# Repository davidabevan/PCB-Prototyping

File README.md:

# PCB-Prototyping
Eagle Cad/Fritzing Footprints for hard to find parts.

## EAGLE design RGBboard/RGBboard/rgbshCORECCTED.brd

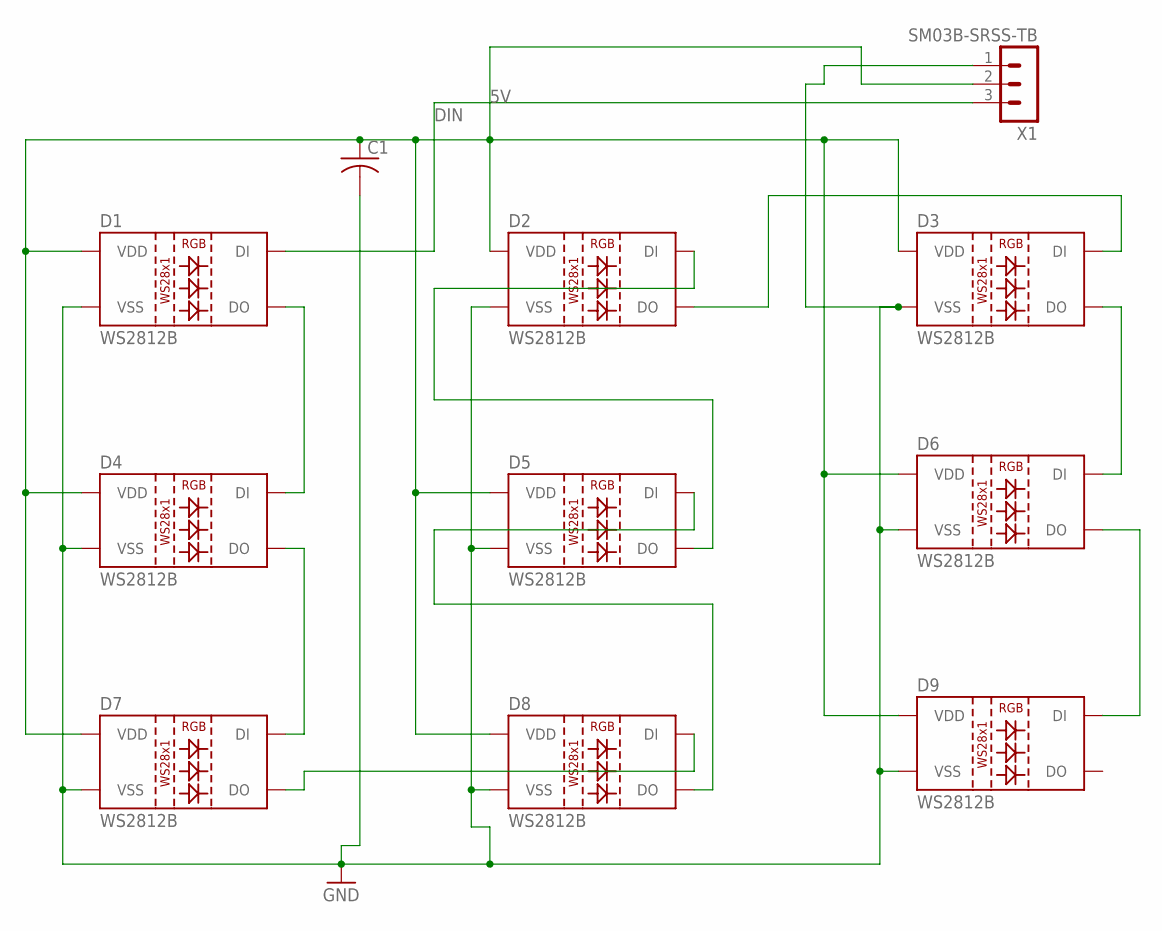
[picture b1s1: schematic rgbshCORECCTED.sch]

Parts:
C1: C-USC0805K; C0805K
D1, D2, D3, D4, D5, D6, D7, D8, D9: WS2812B
X1: SM03B-SRSS-TB

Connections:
5V: C1.1, D1.1 (VDD), D2.1 (VDD), D3.1 (VDD), D4.1 (VDD), D5.1 (VDD), D6.1 (VDD), D7.1 (VDD), D8.1 (VDD), D9.1 (VDD), X1.2
DIN: D1.4 (DI), X1.3
GND: C1.2, D1.3 (VSS), D2.3 (VSS), D3.3 (VSS), D4.3 (VSS), D5.3 (VSS), D6.3 (VSS), D7.3 (VSS), D8.3 (VSS), D9.3 (VSS), X1.1
unnamed: D1.2 (DO), D4.4 (DI)
unnamed: D4.2 (DO), D7.4 (DI)
unnamed: D7.2 (DO), D8.4 (DI)
unnamed: D5.4 (DI), D8.2 (DO)
unnamed: D2.4 (DI), D5.2 (DO)
unnamed: D2.2 (DO), D3.4 (DI)
unnamed: D3.2 (DO), D6.4 (DI)
unnamed: D6.2 (DO), D9.4 (DI)

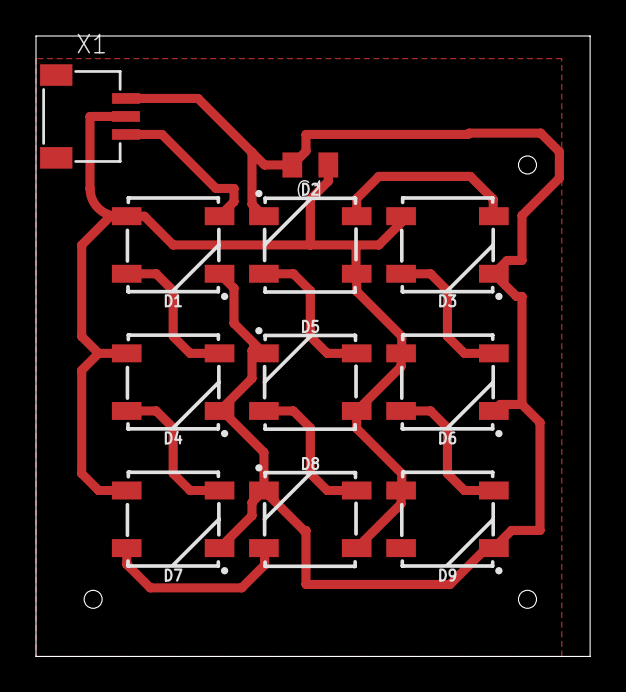
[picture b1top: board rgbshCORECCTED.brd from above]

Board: 2 copper layers, 30.8 x 34.5 mm, 11 parts (0 on the bottom side), 11 nets.

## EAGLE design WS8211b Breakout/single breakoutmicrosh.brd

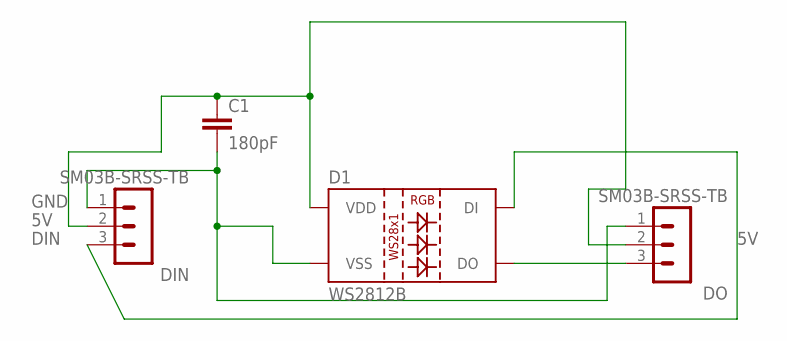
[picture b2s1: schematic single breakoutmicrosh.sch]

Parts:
C1: 180pF; 0603
D1: WS2812B
DIN: SM03B-SRSS-TB
DO: SM03B-SRSS-TB

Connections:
5V: C1.1, D1.1 (VDD), DIN.2, DO.2
DIN: D1.4 (DI), DIN.3
DO: D1.2 (DO), DO.3
GND: C1.2, D1.3 (VSS), DIN.1, DO.1

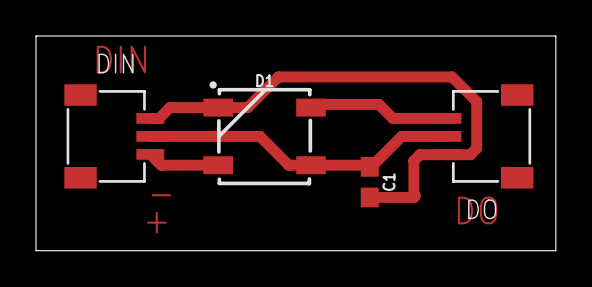
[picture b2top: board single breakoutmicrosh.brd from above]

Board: 2 copper layers, 28.9 x 11.9 mm, 4 parts (0 on the bottom side), 4 nets.

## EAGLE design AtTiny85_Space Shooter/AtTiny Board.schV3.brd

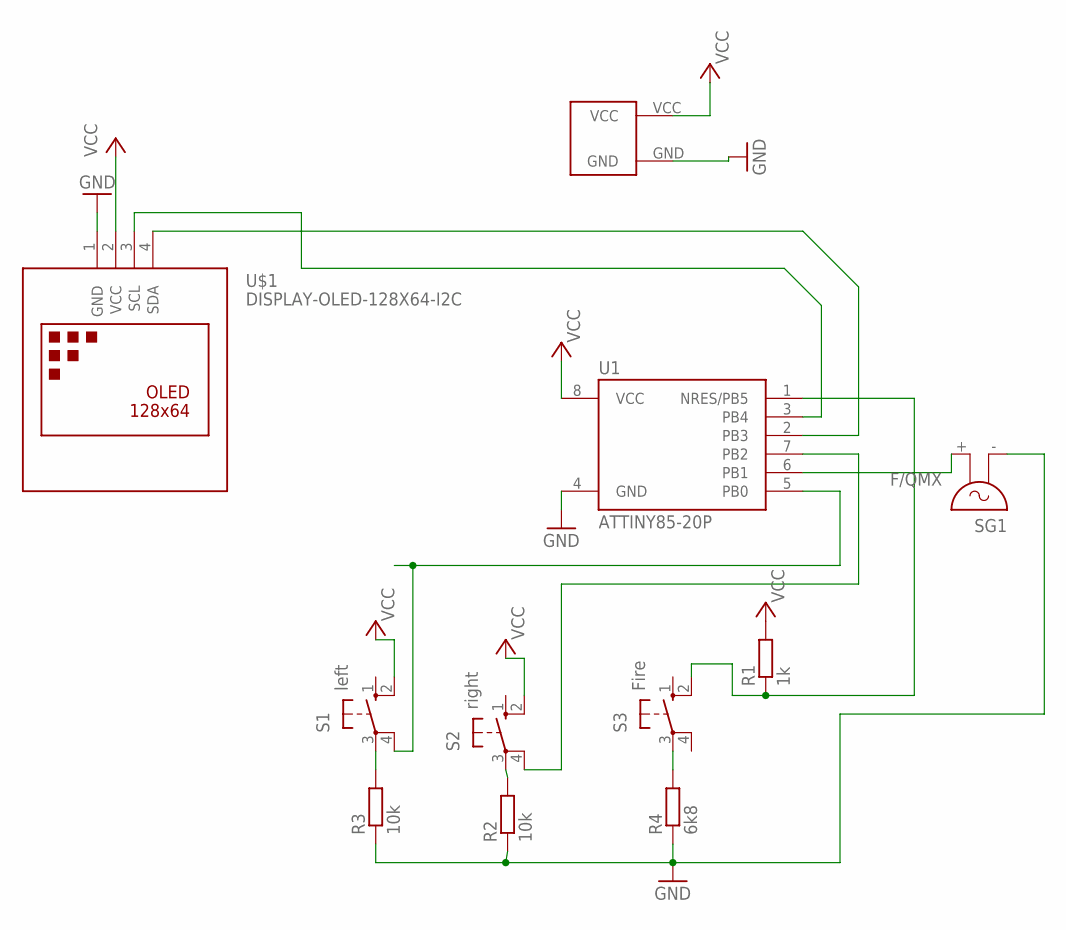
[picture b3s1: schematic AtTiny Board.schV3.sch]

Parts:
R1: 1k; 0204/7
R2, R3: 10k; 0204/7
R4: 6k8; 0204/7
S1: left; B3F-10XX
S2: right; B3F-10XX
S3: Fire; B3F-10XX
SG1: F/QMX
U1: ATTINY85-20P; PDIP08_300MIL
U$1: DISPLAY-OLED-128X64-I2C
U$3: CR2032_19MMDB; CR2032-19MM

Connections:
GND: R2.1, R3.1, R4.1, SG1.- (1), U1.4 (GND), U$1.1 (GND), U$3.GND
unnamed: SG1.+ (2), U1.6 (PB1)
PB0LEFT: S1.4 (P1), U1.5 (PB0)
PB2RIGHT: S2.4 (P1), U1.7 (PB2)
PB5FIRE: R1.1, S3.2 (S1), U1.1 (NRES/PB5)
R2TOGND: R2.2, S2.3
R3TGND: R3.2, S1.3
R4TOGND: R4.2, S3.3
SCL: U1.3 (PB4), U$1.3 (SCL)
SDA: U1.2 (PB3), U$1.4 (SDA)
VCC: R1.2, S1.2 (S1), S2.2 (S1), U1.8 (VCC), U$1.2 (VCC), U$3.VCC

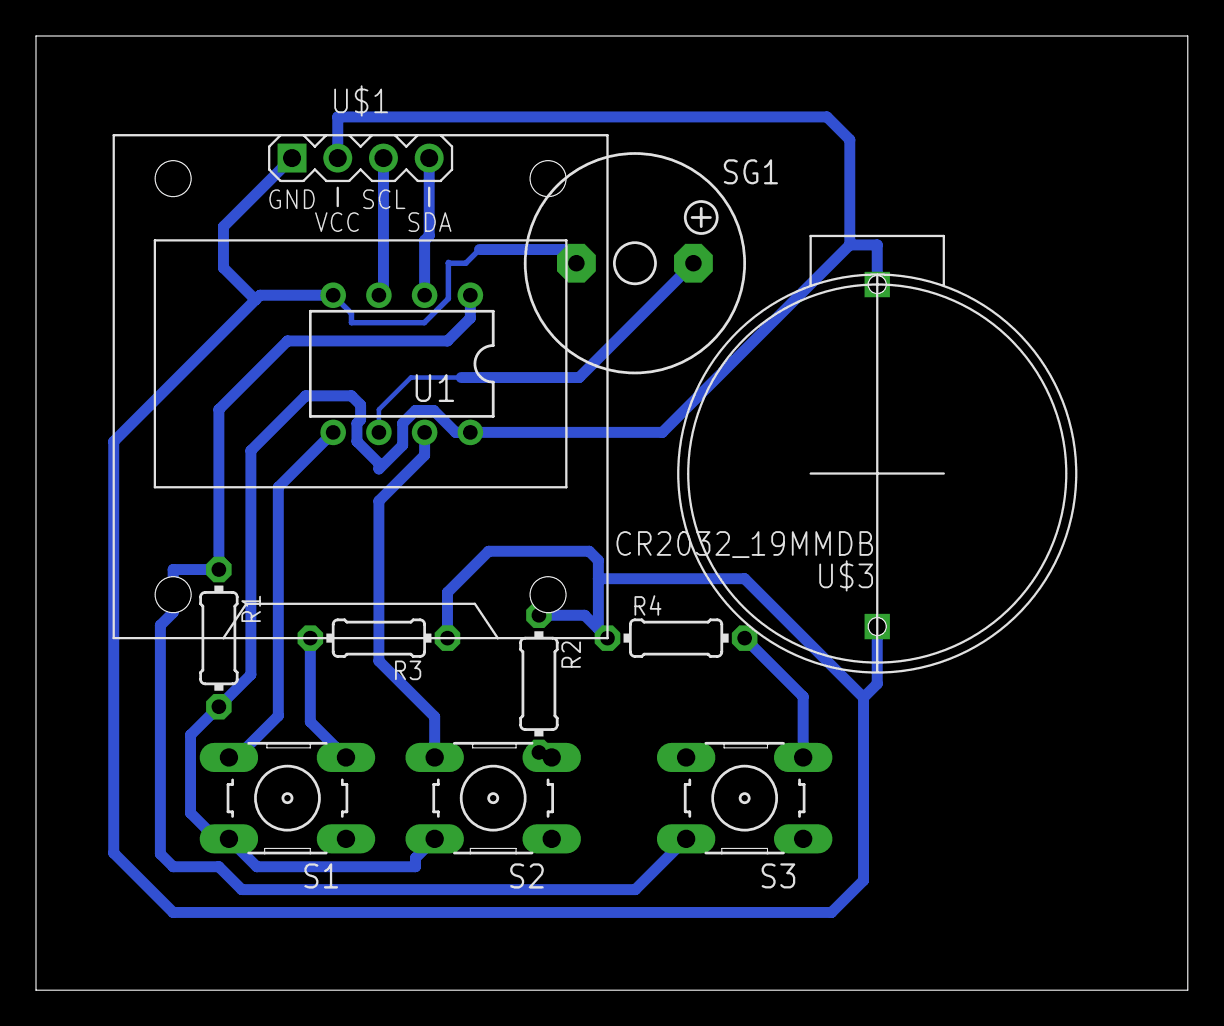
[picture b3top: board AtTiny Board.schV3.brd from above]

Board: 2 copper layers, 64.0 x 53.0 mm, 11 parts (0 on the bottom side), 11 nets.

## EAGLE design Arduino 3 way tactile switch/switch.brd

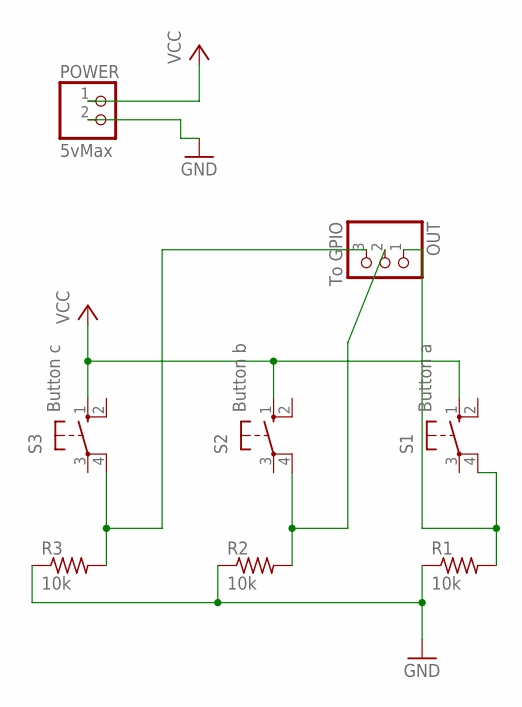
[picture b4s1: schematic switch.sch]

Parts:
OUT: To GPIO; 1X03
POWER: 5vMax; 1X02
R1, R2, R3: 10k; 0204/7
S1: Button a; B3F-10XX
S2: Button b; B3F-10XX
S3: Button c; B3F-10XX

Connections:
GND: POWER.2, R1.1, R2.1, R3.1
unnamed: OUT.3, R3.2, S3.4 (P1)
unnamed: OUT.2, R2.2, S2.4 (P1)
unnamed: OUT.1, R1.2, S1.4 (P1)
VCC: POWER.1, S1.1 (S), S2.1 (S), S3.1 (S)

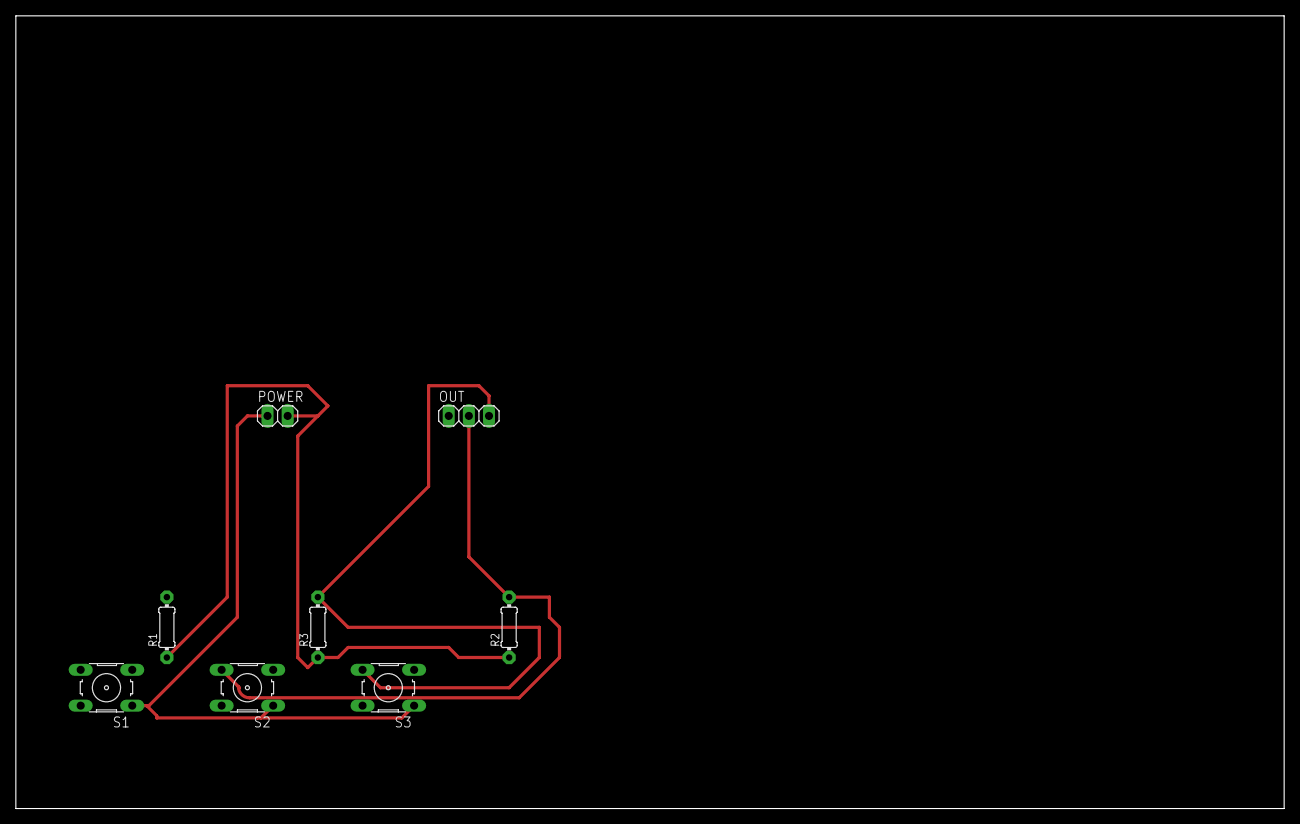
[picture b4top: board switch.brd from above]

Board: 2 copper layers, 160.0 x 100.0 mm, 8 parts (0 on the bottom side), 5 nets.

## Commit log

2019-01-17 contains Arduino ssd1306
2019-01-17 added attiny 85
2019-01-17 added cr2032 holder
2019-01-18 added sparkfun drc and cam files
2019-01-20 Create Home etched boards
2019-01-20 Update Home etched boards
2019-01-21 New ATTiny85 Board design
2019-01-23 created my own esp32 dev board footprint for the 36
2019-01-24 MY NEW VERSION CORRECTED PINS FOR 38 PIN DEV BOARD
2019-02-03 3d version made
2019-02-10 My Managed library
    Added 3d parts work in progress
    Added Silkscreen to 2.2 TFT spi display
2019-02-10 Removed False diameter dimension from silkscreen
2020-02-26 New ws28112b Board
2020-02-26 WS28112b RGB Breakout board single
2020-02-26 Add files via upload
    revised corrected pinouts sh version
2020-03-01 Create Kicad Projects
2020-03-01 kicad circular ws2812b board
2020-03-01 Updated library March 2020
2020-03-09 Places ws2112b leds in a circle decided by radius and led count

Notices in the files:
parts and their libraries:
diy-modules: Released under the Creative Commons Attribution 4.0 International License: http://creativecommons.org/licenses/by/4.0
SparkFun-LED: Licensing: Creative Commons ShareAlike 4.0 International - https://creativecommons.org/licenses/by-sa/4.0
